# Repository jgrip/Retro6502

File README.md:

Migrated to codeberg <https://codeberg.org/jgrip/Retro6502>

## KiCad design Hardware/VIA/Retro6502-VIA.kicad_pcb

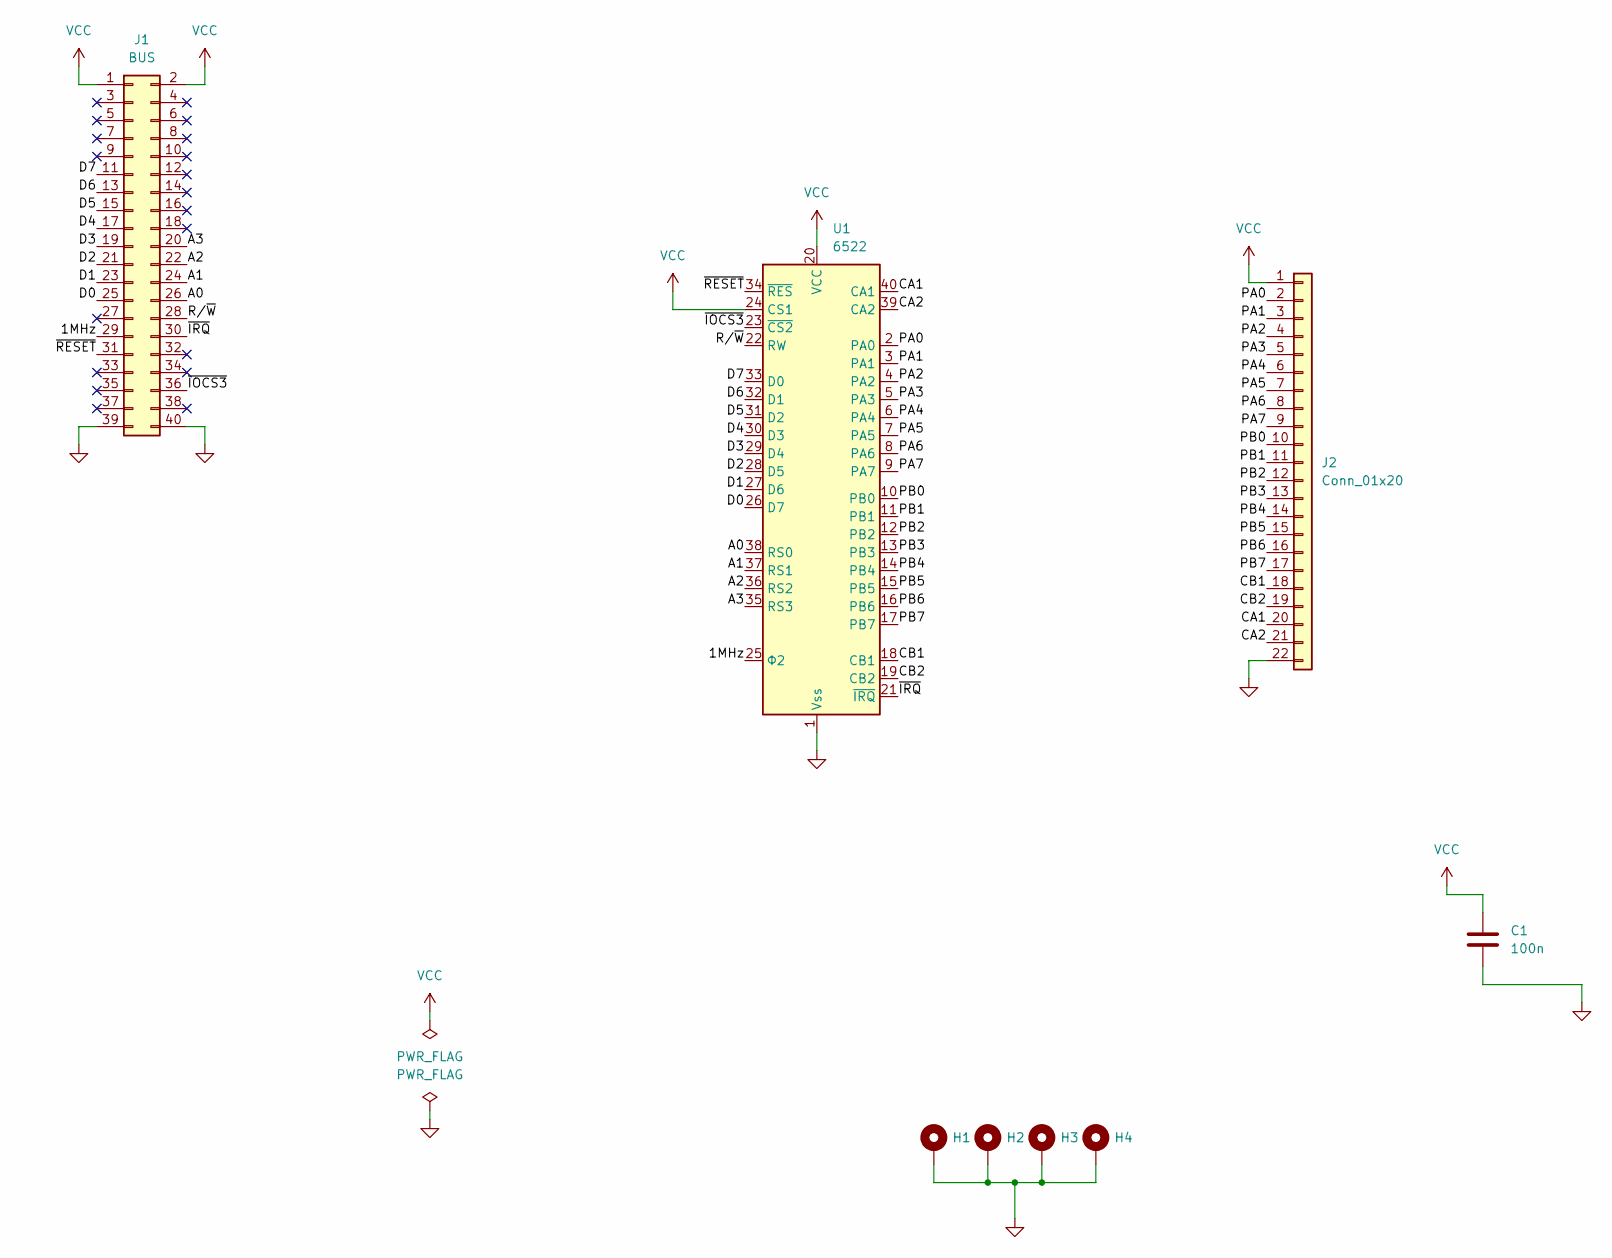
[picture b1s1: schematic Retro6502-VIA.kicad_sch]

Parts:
C1: 100n; C_Disc_D4.3mm_W1.9mm_P5.00mm
H1, H2, H3, H4: MountingHole_Pad; MountingHole_3.2mm_M3_Pad_Via
J1: BUS; PinHeader_2x20_P2.54mm_Vertical; Mouser 649-1012938294004BLF
J2: Conn_01x20; PinHeader_1x22_P2.54mm_Horizontal
U1: 6522; DIP-40_W15.24mm_Socket

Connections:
/1MHz: J1.29, U1.25 (Φ2)
/A0: J1.26, U1.38 (RS0)
/A1: J1.24, U1.37 (RS1)
/A2: J1.22, U1.36 (RS2)
/A3: J1.20, U1.35 (RS3)
/CA1: J2.20, U1.40 (CA1)
/CA2: J2.21, U1.39 (CA2)
/CB1: J2.18, U1.18 (CB1)
/CB2: J2.19, U1.19 (CB2)
/D0: J1.25, U1.26 (D7)
/D1: J1.23, U1.27 (D6)
/D2: J1.21, U1.28 (D5)
/D3: J1.19, U1.29 (D4)
/D4: J1.17, U1.30 (D3)
/D5: J1.15, U1.31 (D2)
/D6: J1.13, U1.32 (D1)
/D7: J1.11, U1.33 (D0)
/PA0: J2.2, U1.2 (PA0)
/PA1: J2.3, U1.3 (PA1)
/PA2: J2.4, U1.4 (PA2)
/PA3: J2.5, U1.5 (PA3)
/PA4: J2.6, U1.6 (PA4)
/PA5: J2.7, U1.7 (PA5)
/PA6: J2.8, U1.8 (PA6)
/PA7: J2.9, U1.9 (PA7)
/PB0: J2.10, U1.10 (PB0)
/PB1: J2.11, U1.11 (PB1)
/PB2: J2.12, U1.12 (PB2)
/PB3: J2.13, U1.13 (PB3)
/PB4: J2.14, U1.14 (PB4)
/PB5: J2.15, U1.15 (PB5)
/PB6: J2.16, U1.16 (PB6)
/PB7: J2.17, U1.17 (PB7)
/R/~W: J1.28, U1.22 (RW)
/~IOCS3: J1.36, U1.23 (~CS2)
/~IRQ: J1.30, U1.21 (~IRQ)
/~RESET: J1.31, U1.34 (~RES)
GND: C1.2, H1.1, H2.1, H3.1, H4.1, J1.39, J1.40, J2.22, U1.1 (Vss)
VCC: C1.1, J1.1, J1.2, J2.1, U1.20 (VCC), U1.24 (CS1)

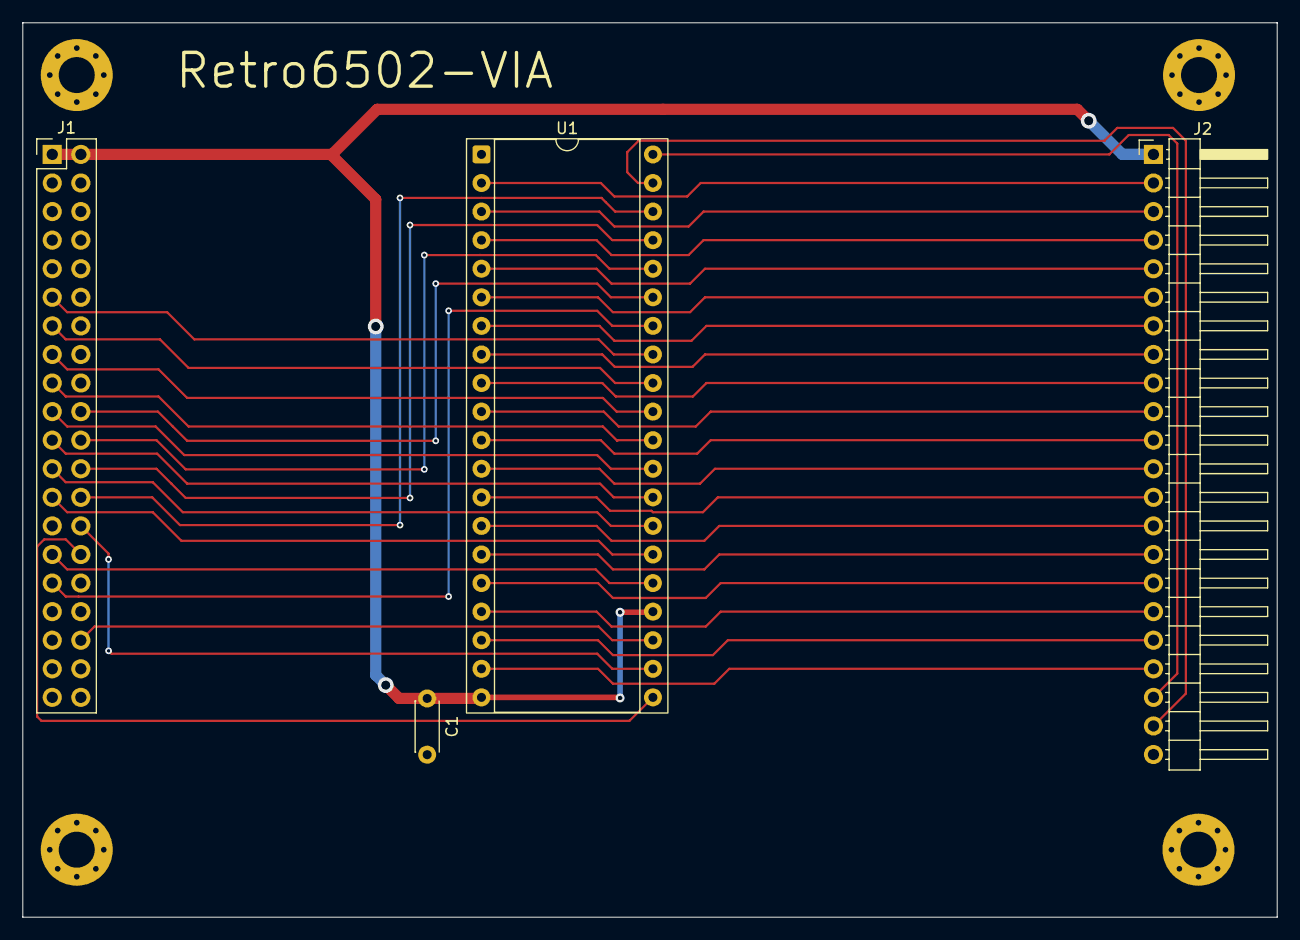
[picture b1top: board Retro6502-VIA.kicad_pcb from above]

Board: 2 copper layers, 111.5 x 79.5 mm, 8 parts (0 on the bottom side), 39 nets.

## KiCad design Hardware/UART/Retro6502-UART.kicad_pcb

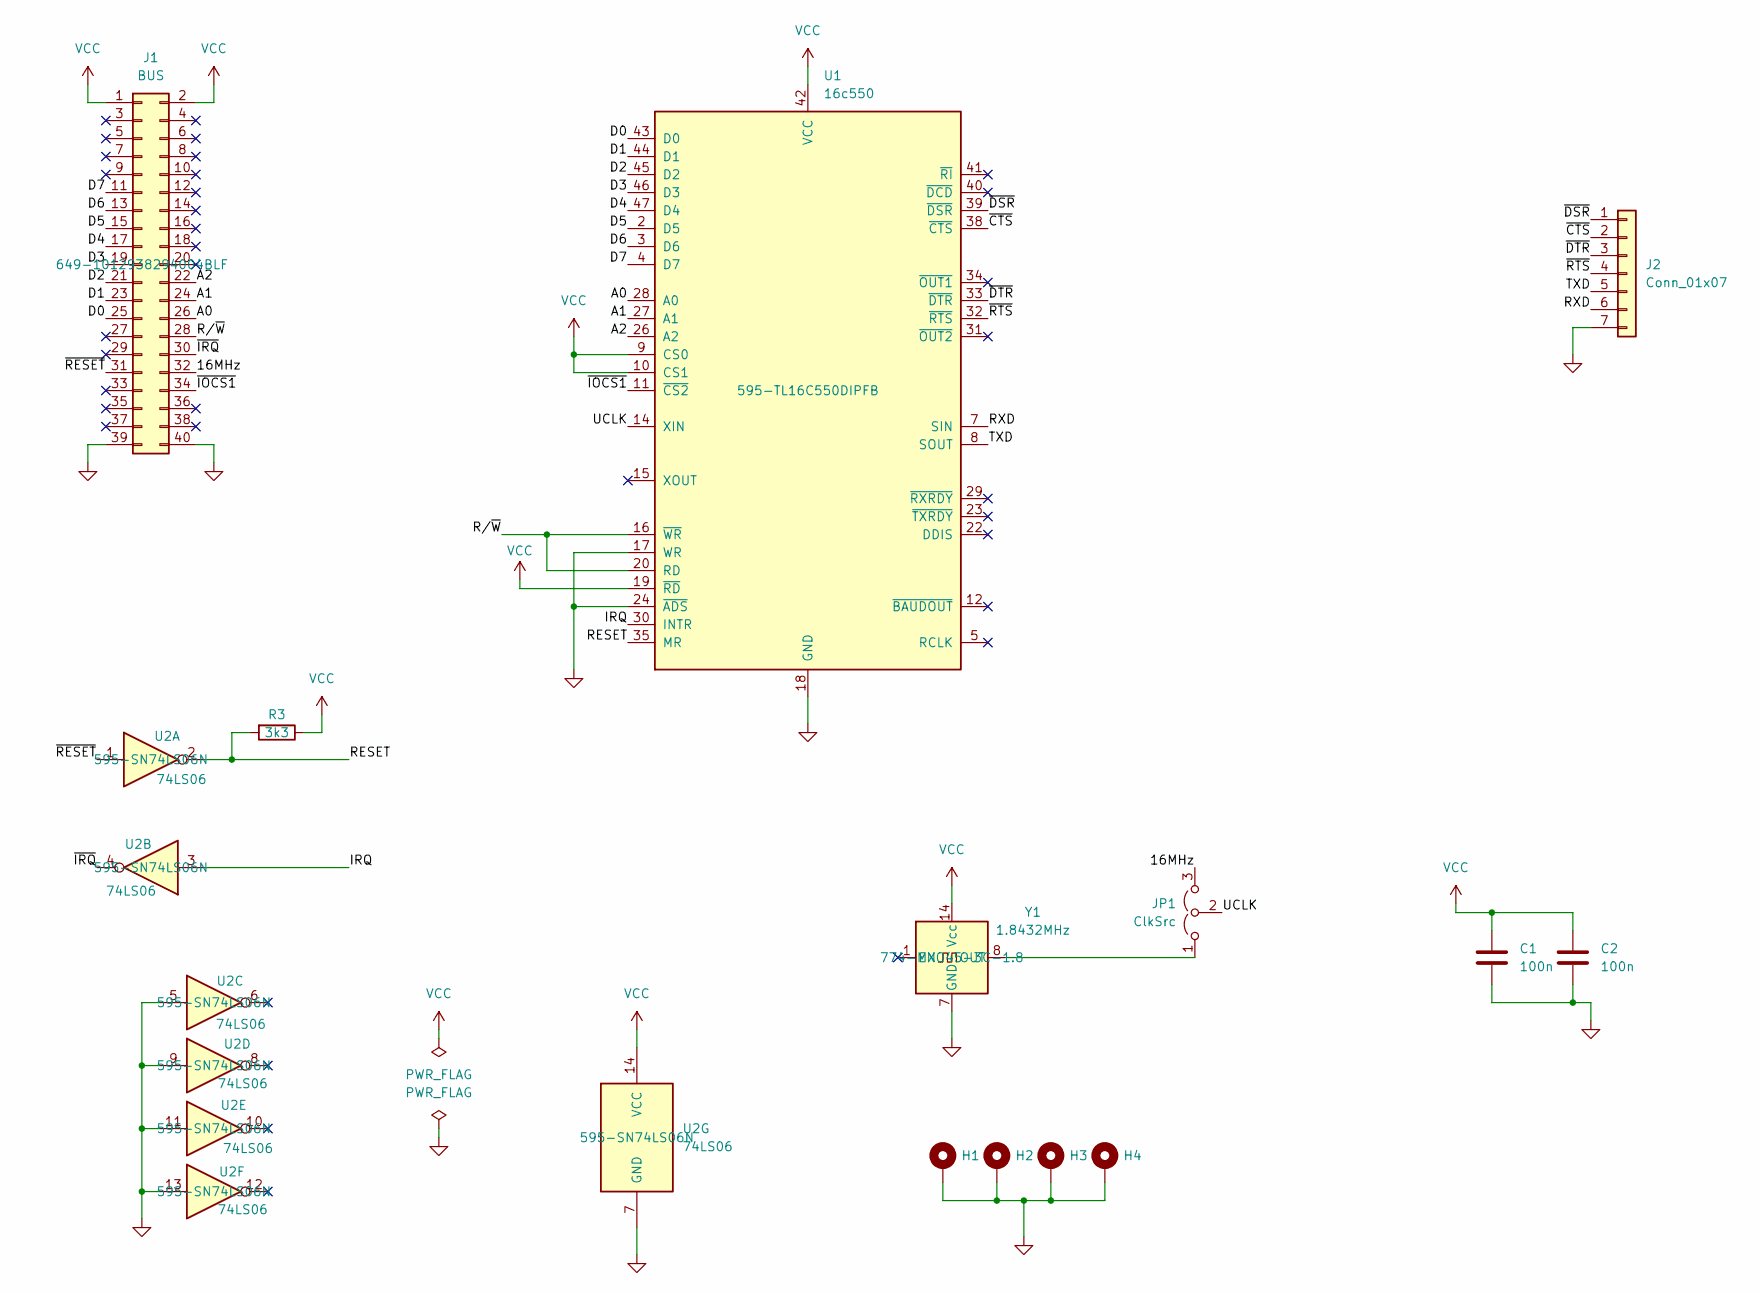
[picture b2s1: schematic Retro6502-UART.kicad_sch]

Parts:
C1, C2: 100n; C_Disc_D4.3mm_W1.9mm_P5.00mm
H1, H2, H3, H4: MountingHole_Pad; MountingHole_3.2mm_M3_Pad_Via
J1: BUS; PinHeader_2x20_P2.54mm_Vertical; Mouser 649-1012938294004BLF
J2: Conn_01x07; PinHeader_1x07_P2.54mm_Horizontal
JP1: ClkSrc; PinHeader_1x03_P2.54mm_Vertical
R3: 3k3; R_Axial_DIN0207_L6.3mm_D2.5mm_P10.16mm_Horizontal
U1: 16c550; TQFP-48_7x7mm_P0.5mm; Mouser 595-TL16C550DIPFB
U2: 74LS06; DIP-14_W7.62mm; Mouser 595-SN74LS06N
Y1: 1.8432MHz; Oscillator_DIP-14; Mouser 774-MXO45-3C-1.8

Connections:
/16MHz: J1.32, JP1.3 (B)
/A0: J1.26, U1.28 (A0)
/A1: J1.24, U1.27 (A1)
/A2: J1.22, U1.26 (A2)
/D0: J1.25, U1.43 (D0)
/D1: J1.23, U1.44 (D1)
/D2: J1.21, U1.45 (D2)
/D3: J1.19, U1.46 (D3)
/D4: J1.17, U1.47 (D4)
/D5: J1.15, U1.2 (D5)
/D6: J1.13, U1.3 (D6)
/D7: J1.11, U1.4 (D7)
/IRQ: U1.30 (INTR), U2.3
/RESET: R3.2, U1.35 (MR), U2.2
/RXD: J2.6, U1.7 (SIN)
/R/~W: J1.28, U1.16 (~WR), U1.20 (RD)
/TXD: J2.5, U1.8 (SOUT)
/UCLK: JP1.2 (C), U1.14 (XIN)
/~CTS: J2.2, U1.38 (~CTS)
/~DSR: J2.1, U1.39 (~DSR)
/~DTR: J2.3, U1.33 (~DTR)
/~IOCS1: J1.34, U1.11 (~CS2)
/~IRQ: J1.30, U2.4
/~RESET: J1.31, U2.1
/~RTS: J2.4, U1.32 (~RTS)
GND: C1.2, C2.2, H1.1, H2.1, H3.1, H4.1, J1.39, J1.40, J2.7, U1.17 (WR), U1.18 (GND), U1.24 (~ADS), U2.5, U2.7 (GND), U2.9, U2.11, U2.13, Y1.7 (GND)
unnamed: JP1.1 (A), Y1.8 (OUT)
VCC: C1.1, C2.1, J1.1, J1.2, R3.1, U1.9 (CS0), U1.10 (CS1), U1.19 (~RD), U1.42 (VCC), U2.14 (VCC), Y1.14 (Vcc)

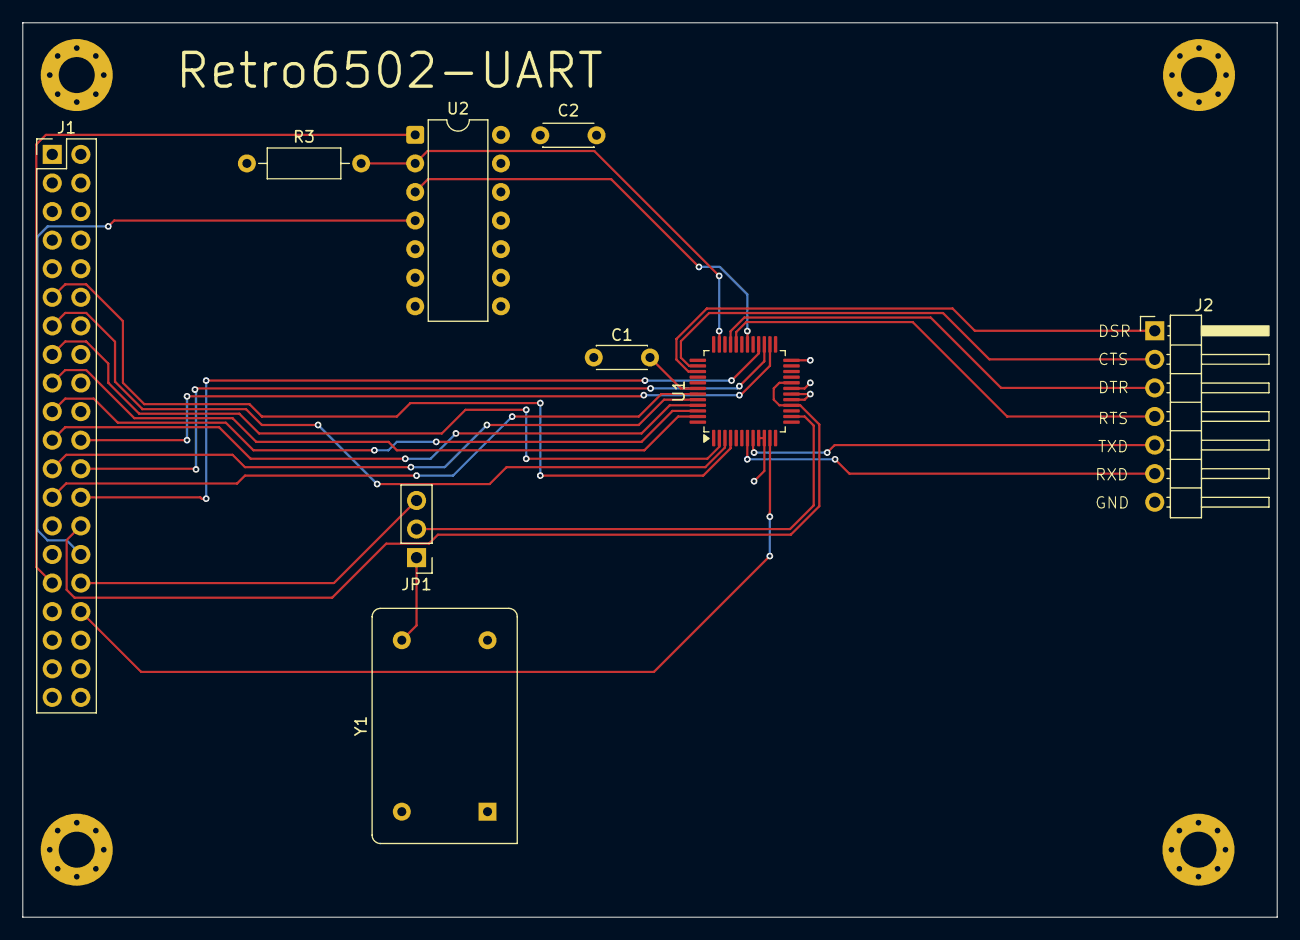
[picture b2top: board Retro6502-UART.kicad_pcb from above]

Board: 4 copper layers, 111.5 x 79.5 mm, 13 parts (0 on the bottom side), 28 nets.

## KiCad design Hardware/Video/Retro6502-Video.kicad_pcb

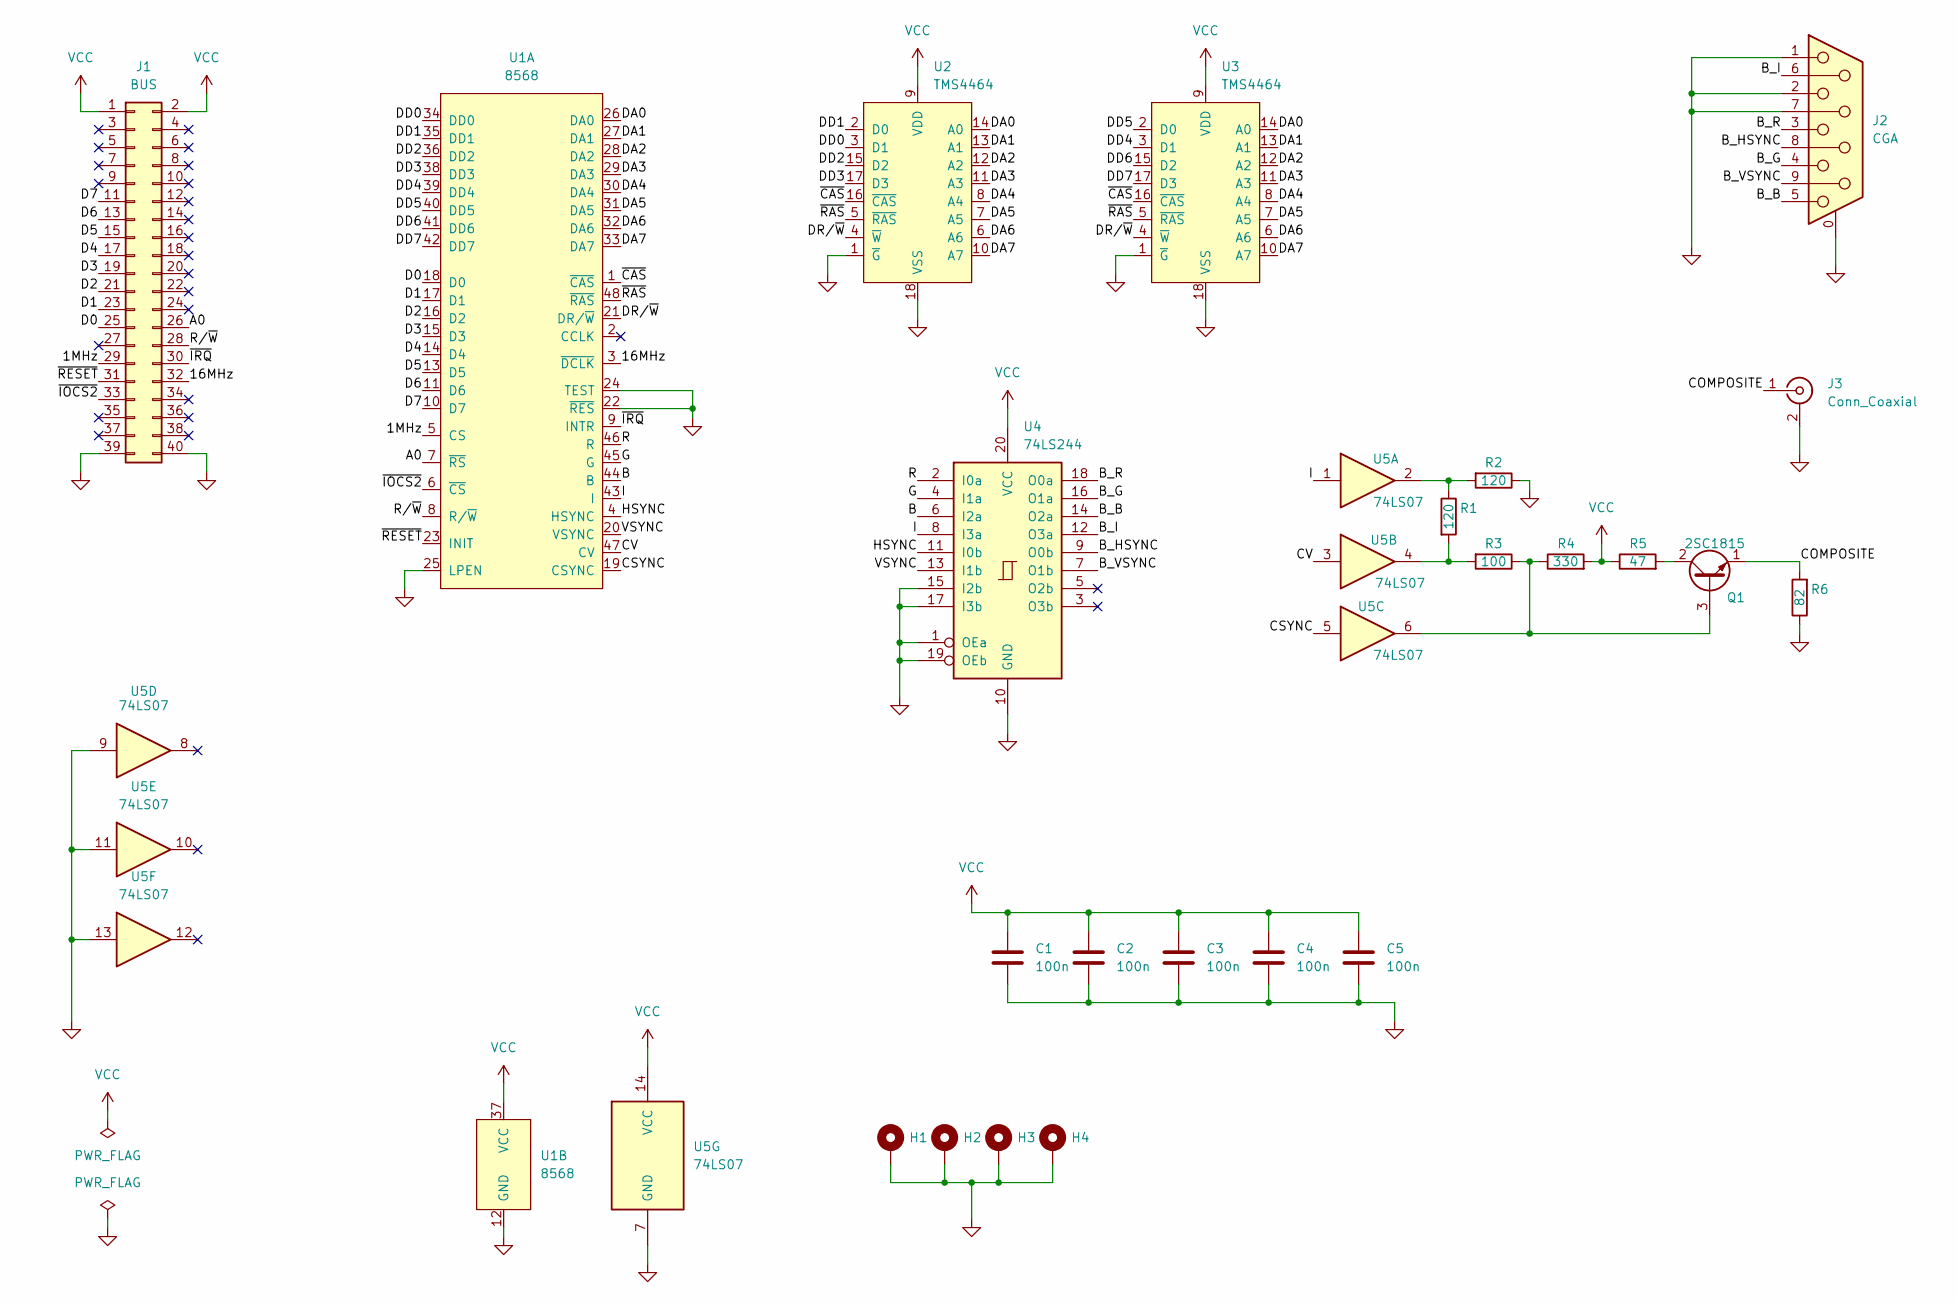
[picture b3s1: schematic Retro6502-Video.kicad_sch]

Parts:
C1, C2, C3, C4, C5: 100n; C_Disc_D4.3mm_W1.9mm_P5.00mm
H1, H2, H3, H4: MountingHole_Pad; MountingHole_3.2mm_M3_Pad_Via
J1: BUS; PinHeader_2x20_P2.54mm_Vertical; Mouser 649-1012938294004BLF
J2: CGA; DSUB-9_Female_Horizontal_P2.77x2.84mm_EdgePinOffset7.70mm_H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; Mouser 636-182-009-213R181
J3: Conn_Coaxial; SwitchCraft-PJRA; Mouser 502-PJRAN1X1U04AUX
Q1: 2SC1815; TO-92L_Inline_Wide; Mouser 512-KSC1815YTA
R1, R2: 120; R_Axial_DIN0207_L6.3mm_D2.5mm_P10.16mm_Horizontal
R3: 100; R_Axial_DIN0207_L6.3mm_D2.5mm_P10.16mm_Horizontal
R4: 330; R_Axial_DIN0207_L6.3mm_D2.5mm_P10.16mm_Horizontal
R5: 47; R_Axial_DIN0207_L6.3mm_D2.5mm_P10.16mm_Horizontal
R6: 82; R_Axial_DIN0207_L6.3mm_D2.5mm_P10.16mm_Horizontal
U1: 8568; DIP-48_W15.24mm_Socket; Mouser 517-4848-6000-CP
U2, U3: TMS4464; DIP-18_W7.62mm_Socket
U4: 74LS244; DIP-20_W7.62mm; Mouser 595-SN74LS244N
U5: 74LS07; DIP-14_W7.62mm; Mouser 595-SN74LS07N

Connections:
/1MHz: J1.29, U1.5 (CS)
/16MHz: J1.32, U1.3 (~DCLK)
/A0: J1.26, U1.7 (~RS)
/B: U1.44 (B), U4.6 (I2a)
/B_B: J2.5, U4.14 (O2a)
/B_G: J2.4, U4.16 (O1a)
/B_HSYNC: J2.8, U4.9 (O0b)
/B_I: J2.6, U4.12 (O3a)
/B_R: J2.3, U4.18 (O0a)
/B_VSYNC: J2.9, U4.7 (O1b)
/COMPOSITE: J3.1 (In), Q1.1 (E), R6.2
/CSYNC: U1.19 (CSYNC), U5.5
/CV: U1.47 (CV), U5.3
/D0: J1.25, U1.18 (D0)
/D1: J1.23, U1.17 (D1)
/D2: J1.21, U1.16 (D2)
/D3: J1.19, U1.15 (D3)
/D4: J1.17, U1.14 (D4)
/D5: J1.15, U1.13 (D5)
/D6: J1.13, U1.11 (D6)
/D7: J1.11, U1.10 (D7)
/DA0: U1.26 (DA0), U2.14 (A0), U3.14 (A0)
/DA1: U1.27 (DA1), U2.13 (A1), U3.13 (A1)
/DA2: U1.28 (DA2), U2.12 (A2), U3.12 (A2)
/DA3: U1.29 (DA3), U2.11 (A3), U3.11 (A3)
/DA4: U1.30 (DA4), U2.8 (A4), U3.8 (A4)
/DA5: U1.31 (DA5), U2.7 (A5), U3.7 (A5)
/DA6: U1.32 (DA6), U2.6 (A6), U3.6 (A6)
/DA7: U1.33 (DA7), U2.10 (A7), U3.10 (A7)
/DD0: U1.34 (DD0), U2.3 (D1)
/DD1: U1.35 (DD1), U2.2 (D0)
/DD2: U1.36 (DD2), U2.15 (D2)
/DD3: U1.38 (DD3), U2.17 (D3)
/DD4: U1.39 (DD4), U3.3 (D1)
/DD5: U1.40 (DD5), U3.2 (D0)
/DD6: U1.41 (DD6), U3.15 (D2)
/DD7: U1.42 (DD7), U3.17 (D3)
/DR/~W: U1.21 (DR/~W), U2.4 (~W), U3.4 (~W)
/G: U1.45 (G), U4.4 (I1a)
/HSYNC: U1.4 (HSYNC), U4.11 (I0b)
/I: U1.43 (I), U4.8 (I3a), U5.1
/R: U1.46 (R), U4.2 (I0a)
/R/~W: J1.28, U1.8 (R/~W)
/VSYNC: U1.20 (VSYNC), U4.13 (I1b)
/~CAS: U1.1 (~CAS), U2.16 (~CAS), U3.16 (~CAS)
/~IOCS2: J1.33, U1.6 (~CS)
/~IRQ: J1.30, U1.9 (INTR)
/~RAS: U1.48 (~RAS), U2.5 (~RAS), U3.5 (~RAS)
/~RESET: J1.31, U1.23 (INIT)
GND: C1.2, C2.2, C3.2, C4.2, C5.2, H1.1, H2.1, H3.1, H4.1, J1.39, J1.40, J2.0 (PAD), J2.1, J2.2, J2.7, J3.2 (Ext), R2.1, R6.1, U1.12 (GND), U1.22 (~RES), U1.24 (TEST), U1.25 (LPEN), U2.1 (~G), U2.18 (VSS), U3.1 (~G), U3.18 (VSS), U4.1 (OEa), U4.10 (GND), U4.15 (I2b), U4.17 (I3b), U4.19 (OEb), U5.7 (GND), U5.9, U5.11, U5.13
unnamed: Q1.3 (B), R3.1, R4.1, U5.6
unnamed: Q1.2 (C), R5.2
unnamed: R1.1, R2.2, U5.2
unnamed: R1.2, R3.2, U5.4
VCC: C1.1, C2.1, C3.1, C4.1, C5.1, J1.1, J1.2, R4.2, R5.1, U1.37 (VCC), U2.9 (VDD), U3.9 (VDD), U4.20 (VCC), U5.14 (VCC)

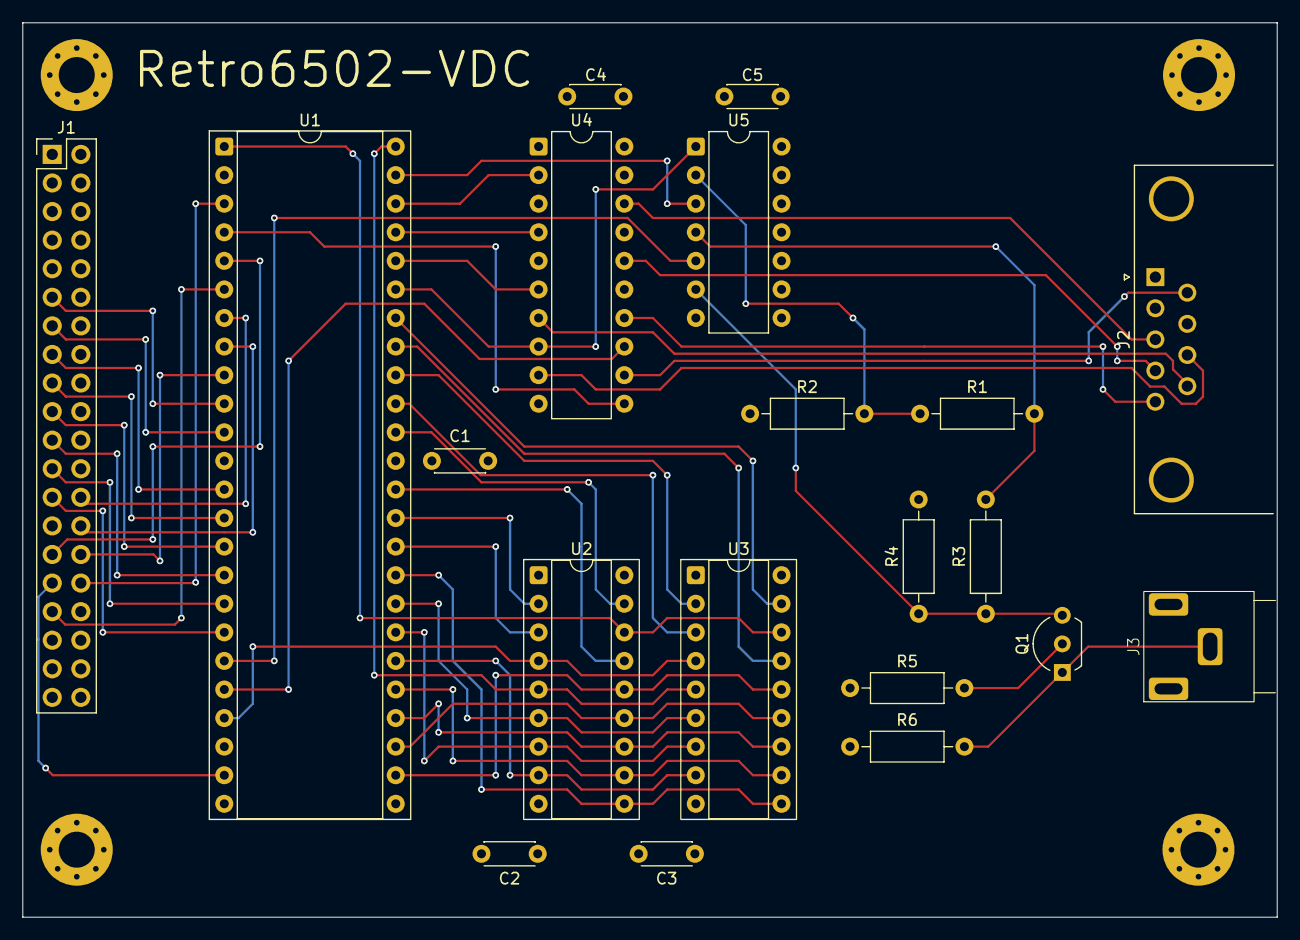
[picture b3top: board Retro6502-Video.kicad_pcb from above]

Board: 4 copper layers, 111.5 x 79.5 mm, 24 parts (0 on the bottom side), 55 nets.

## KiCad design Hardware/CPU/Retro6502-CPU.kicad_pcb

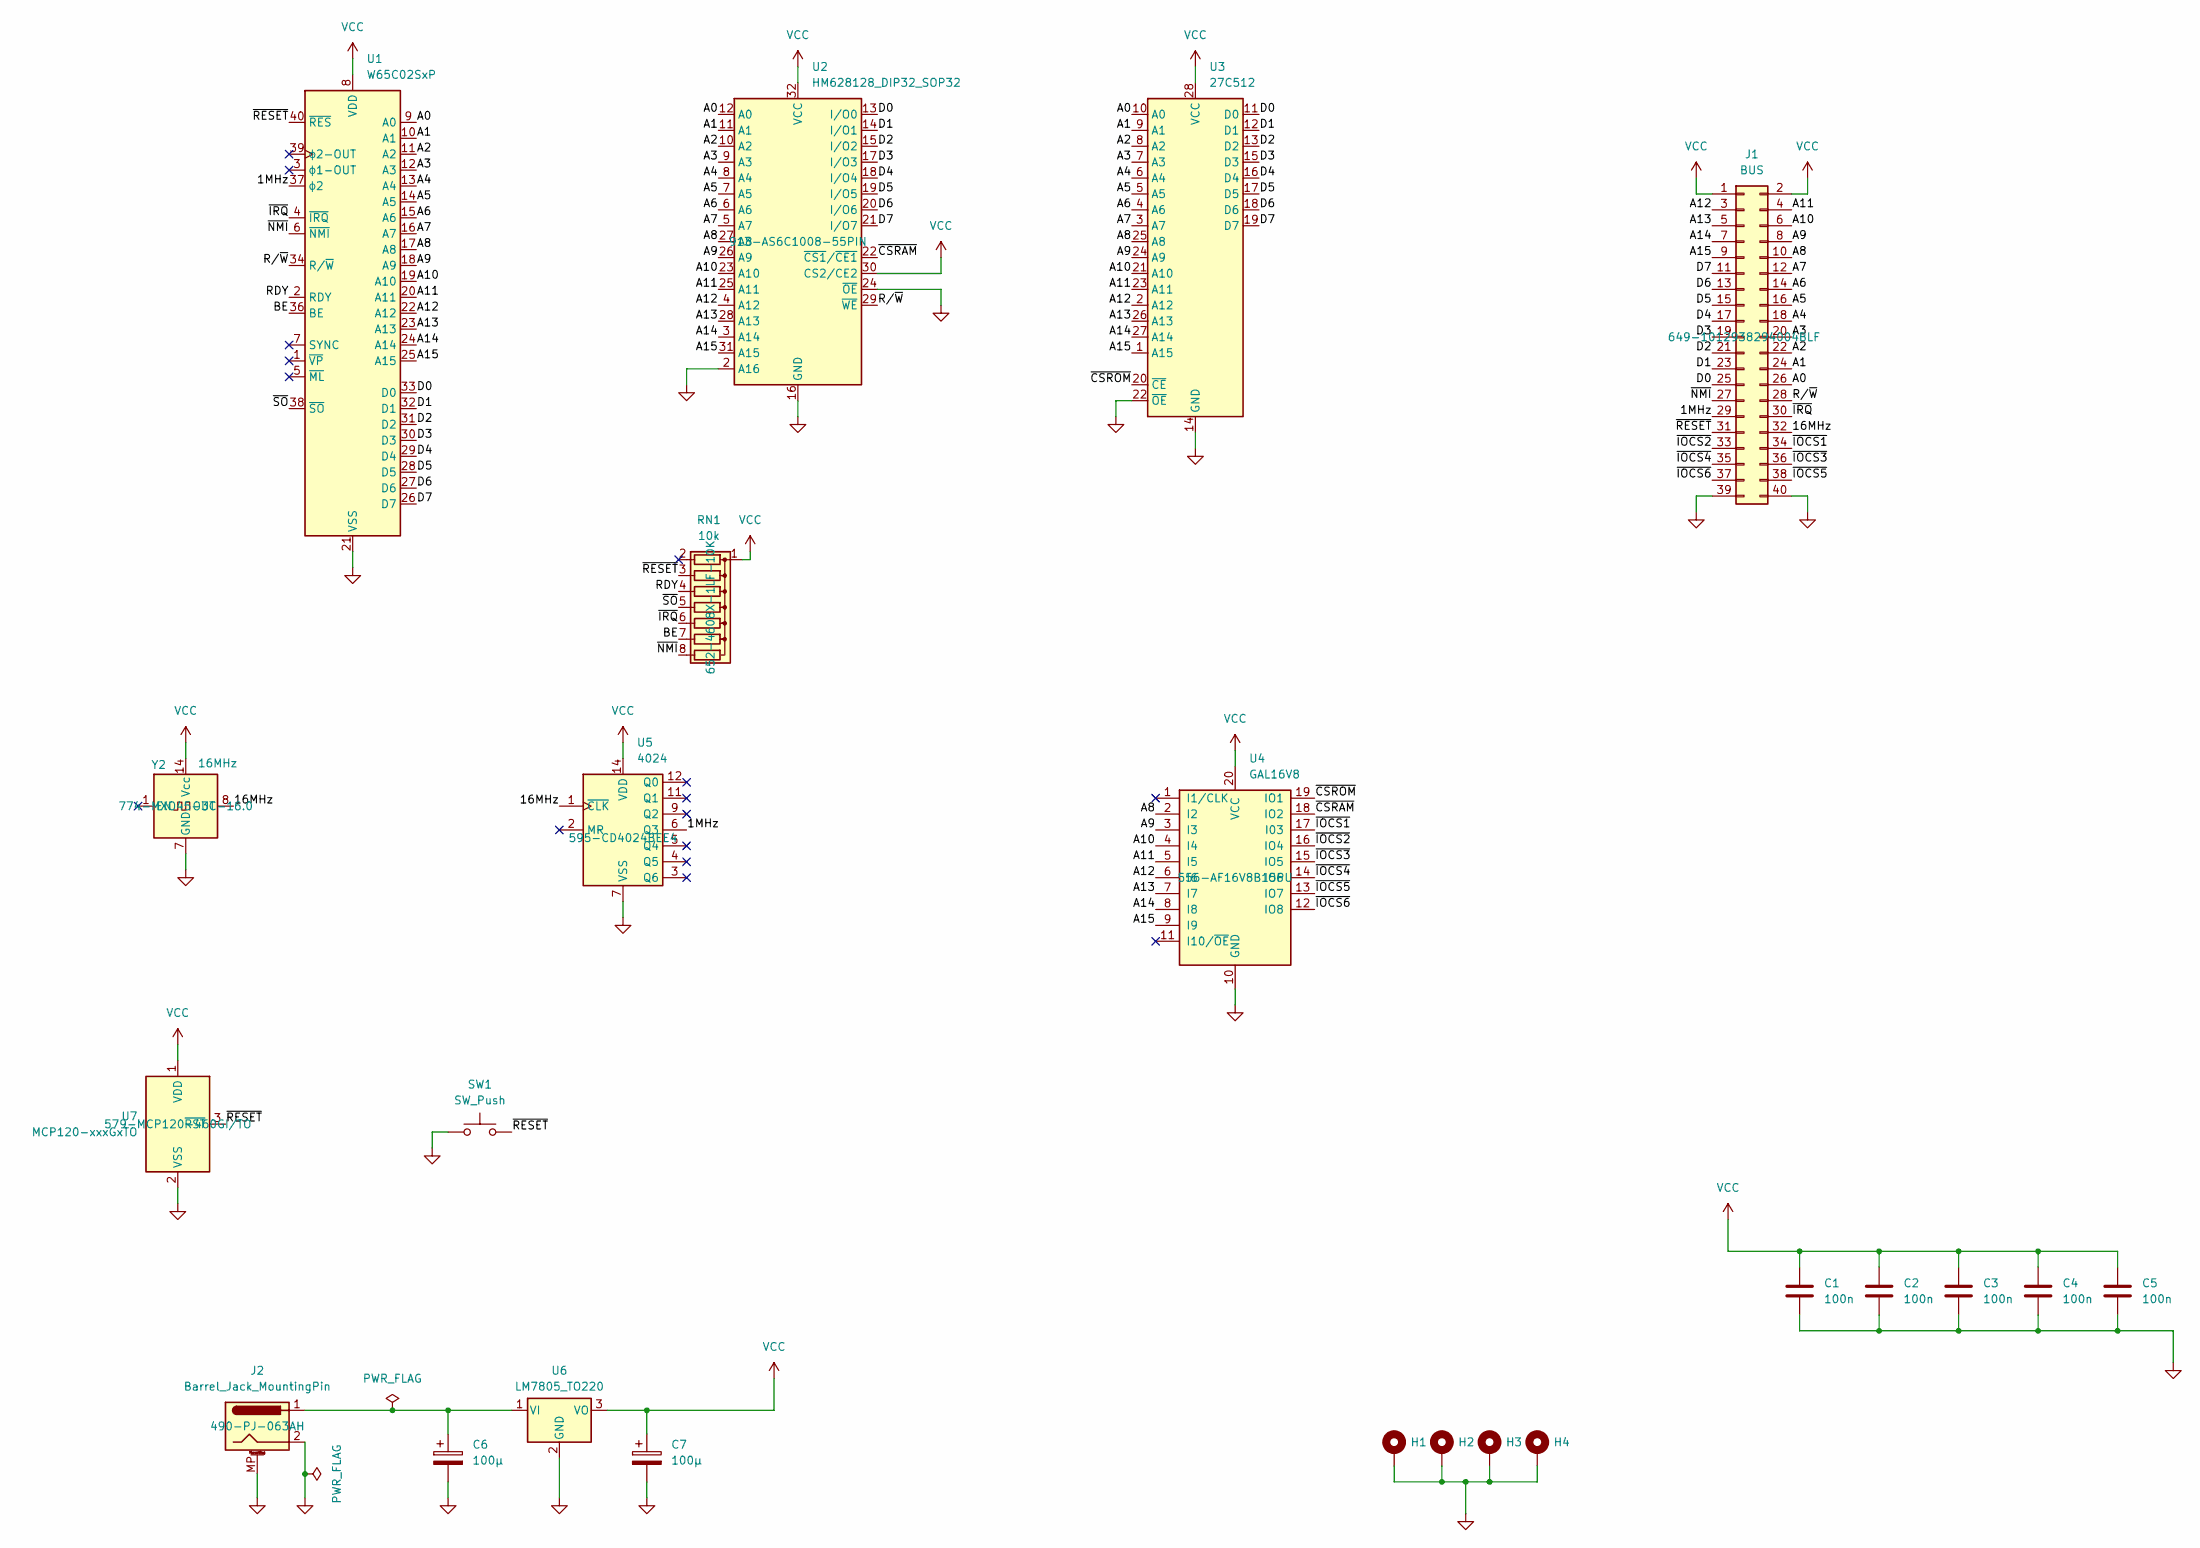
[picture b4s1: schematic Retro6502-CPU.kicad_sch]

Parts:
C1, C2, C3, C4, C5: 100n; C_Disc_D4.3mm_W1.9mm_P5.00mm
C6, C7: 100μ; CP_Radial_D5.0mm_P2.50mm
H1, H2, H3, H4: MountingHole_Pad; MountingHole_3.2mm_M3_Pad_Via
J1: BUS; PinHeader_2x20_P2.54mm_Vertical; Mouser 649-1012938294004BLF
J2: Barrel_Jack_MountingPin; BarrelJack_CUI_PJ-063AH_Horizontal; Mouser 490-PJ-063AH
RN1: 10k; R_Array_SIP8; Mouser 652-4608X-1LF-10K
SW1: SW_Push; SW_PUSH_6mm_H4.3mm
U1: W65C02SxP; DIP-40_W15.24mm_Socket; Mouser 955-W65C02S6TQG-14
U2: HM628128_DIP32_SOP32; DIP-32_W15.24mm_Socket; Mouser 913-AS6C1008-55PIN
U3: 27C512; DIP-28_W15.24mm
U4: GAL16V8; DIP-20_W7.62mm_Socket; Mouser 556-AF16V8B15PU
U5: 4024; DIP-14_W7.62mm; Mouser 595-CD4024BEE4
U6: LM7805_TO220; TO-220-3_Vertical
U7: MCP120-xxxGxTO; TO-92_Inline; Mouser 579-MCP120-460GI/TO
Y2: 16MHz; Oscillator_DIP-14; Mouser 774-MXO45-3C-16.0

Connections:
/1MHz: J1.29, U1.37 (ϕ2), U5.6 (Q3)
/16MHz: J1.32, U5.1 (~CLK), Y2.8 (OUT)
/A0: J1.26, U1.9 (A0), U2.12 (A0), U3.10 (A0)
/A1: J1.24, U1.10 (A1), U2.11 (A1), U3.9 (A1)
/A2: J1.22, U1.11 (A2), U2.10 (A2), U3.8 (A2)
/A3: J1.20, U1.12 (A3), U2.9 (A3), U3.7 (A3)
/A4: J1.18, U1.13 (A4), U2.8 (A4), U3.6 (A4)
/A5: J1.16, U1.14 (A5), U2.7 (A5), U3.5 (A5)
/A6: J1.14, U1.15 (A6), U2.6 (A6), U3.4 (A6)
/A7: J1.12, U1.16 (A7), U2.5 (A7), U3.3 (A7)
/A8: J1.10, U1.17 (A8), U2.27 (A8), U3.25 (A8), U4.2 (I2)
/A9: J1.8, U1.18 (A9), U2.26 (A9), U3.24 (A9), U4.3 (I3)
/A10: J1.6, U1.19 (A10), U2.23 (A10), U3.21 (A10), U4.4 (I4)
/A11: J1.4, U1.20 (A11), U2.25 (A11), U3.23 (A11), U4.5 (I5)
/A12: J1.3, U1.22 (A12), U2.4 (A12), U3.2 (A12), U4.6 (I6)
/A13: J1.5, U1.23 (A13), U2.28 (A13), U3.26 (A13), U4.7 (I7)
/A14: J1.7, U1.24 (A14), U2.3 (A14), U3.27 (A14), U4.8 (I8)
/A15: J1.9, U1.25 (A15), U2.31 (A15), U3.1 (A15), U4.9 (I9)
/BE: RN1.7 (R6), U1.36 (BE)
/D0: J1.25, U1.33 (D0), U2.13 (I/O0), U3.11 (D0)
/D1: J1.23, U1.32 (D1), U2.14 (I/O1), U3.12 (D1)
/D2: J1.21, U1.31 (D2), U2.15 (I/O2), U3.13 (D2)
/D3: J1.19, U1.30 (D3), U2.17 (I/O3), U3.15 (D3)
/D4: J1.17, U1.29 (D4), U2.18 (I/O4), U3.16 (D4)
/D5: J1.15, U1.28 (D5), U2.19 (I/O5), U3.17 (D5)
/D6: J1.13, U1.27 (D6), U2.20 (I/O6), U3.18 (D6)
/D7: J1.11, U1.26 (D7), U2.21 (I/O7), U3.19 (D7)
/RDY: RN1.4 (R3), U1.2 (RDY)
/R/~W: J1.28, U1.34 (R/~W), U2.29 (~WE)
/~CSRAM: U2.22 (~CS1/~CE1), U4.18 (IO2)
/~CSROM: U3.20 (~CE), U4.19 (IO1)
/~IOCS1: J1.34, U4.17 (I03)
/~IOCS2: J1.33, U4.16 (IO4)
/~IOCS3: J1.36, U4.15 (IO5)
/~IOCS4: J1.35, U4.14 (IO6)
/~IOCS5: J1.38, U4.13 (IO7)
/~IOCS6: J1.37, U4.12 (IO8)
/~IRQ: J1.30, RN1.6 (R5), U1.4 (~IRQ)
/~NMI: J1.27, RN1.8 (R7), U1.6 (~NMI)
/~RESET: J1.31, RN1.3 (R2), SW1.2, U1.40 (~RES), U7.3 (~RST)
/~SO: RN1.5 (R4), U1.38 (~SO)
GND: C1.2, C2.2, C3.2, C4.2, C5.2, C6.2, C7.2, H1.1, H2.1, H3.1, H4.1, J1.39, J1.40, J2.2, J2.MP (MountPin), SW1.1, U1.21 (VSS), U2.2 (A16), U2.16 (GND), U2.24 (~OE), U3.14 (GND), U3.22 (~OE), U4.10 (GND), U5.7 (VSS), U6.2 (GND), U7.2 (VSS), Y2.7 (GND)
unnamed: C6.1, J2.1, U6.1 (VI)
VCC: C1.1, C2.1, C3.1, C4.1, C5.1, C7.1, J1.1, J1.2, RN1.1 (common), U1.8 (VDD), U2.30 (CS2/CE2), U2.32 (VCC), U3.28 (VCC), U4.20 (VCC), U5.14 (VDD), U6.3 (VO), U7.1 (VDD), Y2.14 (Vcc)

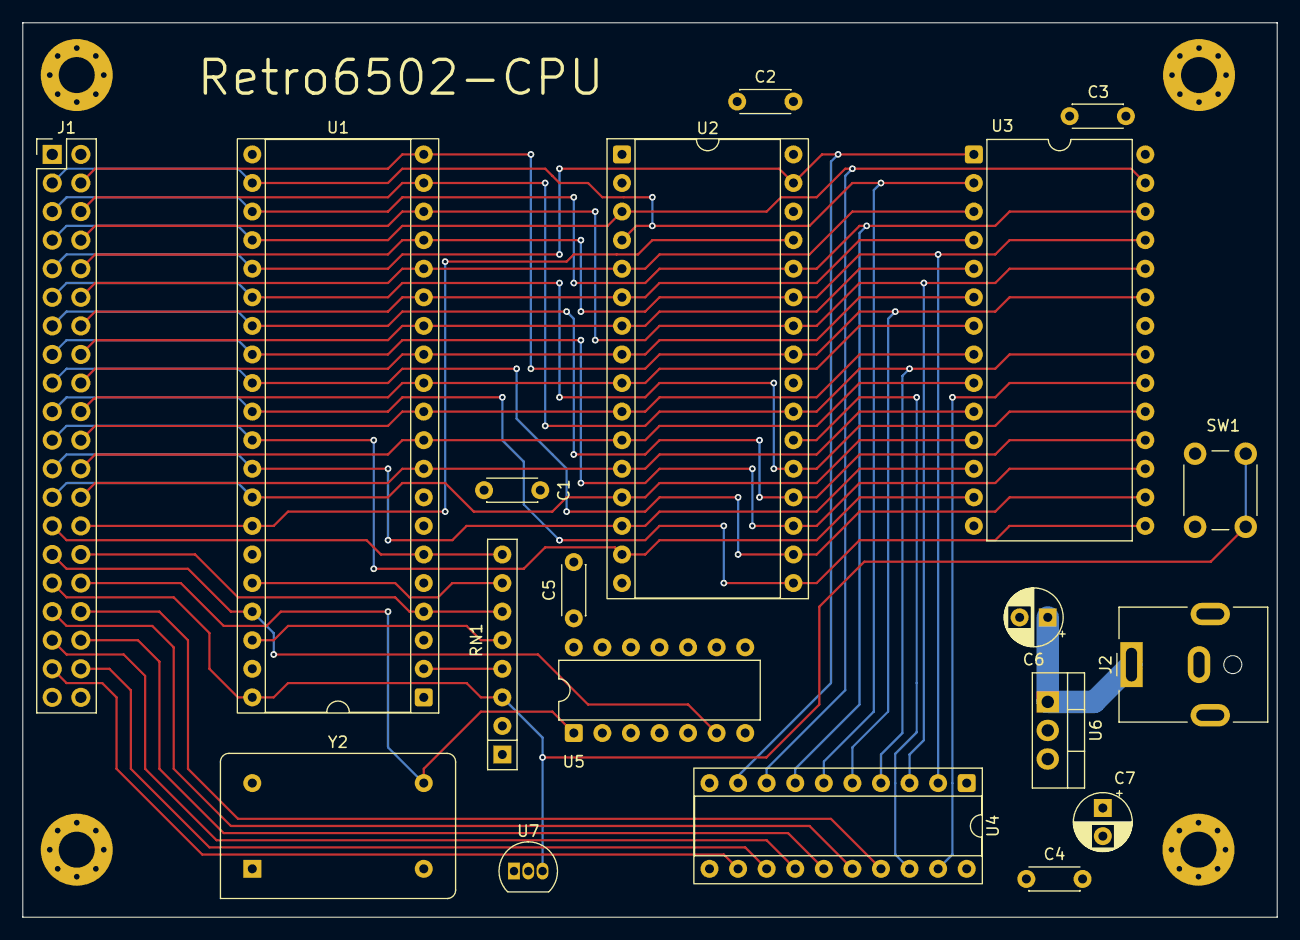
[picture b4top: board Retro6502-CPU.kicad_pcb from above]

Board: 4 copper layers, 111.5 x 79.5 mm, 23 parts (0 on the bottom side), 44 nets.
